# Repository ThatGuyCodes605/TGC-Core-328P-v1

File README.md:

# TGC-Core-328P-v1

## Overview
The **TGC-Core-328P-v1** is an open-source hardware development board. Based on the file naming and standard conventions, it is designed around the "Mega" architecture (typically the Microchip ATme[...] 

This repository contains the complete set of KiCad EDA files necessary to view, modify and manufacture the printed circuit board (PCB).

---

## Features
* **Architecture:** Mega-compatible (ATmega2560) platform.
* **Modern Connectivity:** Upgraded from the legacy USB Type-B to a robust **USB-C 2.0** connector.
* **Native KiCad Design:** Fully designed using KiCad, allowing for easy community modification and inspection.
* **Standard Form Factor:** Designed for compatibility with existing shields and standard development workflows.

---

## Repository Structure

The project is entirely self-contained within the following KiCad design files:

| File Name | Description |
| :--- | :--- |
| `TGC-Core-devboard-Mega-v1.kicad_pro` | The main **KiCad Project file**. Open this file to load the entire project space. |
| `TGC-Core-devboard-Mega-v1.kicad_sch` | The **Schematic file**. Contains the logical connections, components (like the USB-C plug and SW_Push buttons), and wiring. |
| `TGC-Core-devboard-Mega-v1.kicad_pcb` | The **PCB Layout file**. Contains the physical board routing, copper layers, and silkscreen definitions. |
| `TGC-Core-devboard-Mega-v1.png` | A visual render or top-down image of the board design. |

---

## Hardware Specifications (Expected)

*Based on standard Mega-compatible board parameters:*

* **Microcontroller:** ATmega2560 (8-bit AVR)
* **Operating Voltage:** 5V
* **Clock Speed:** 16 MHz
* **Digital I/O Pins:** 54 (of which 15 provide PWM output)
* **Analog Input Pins:** 16
* **Hardware Serial Ports (UARTs):** 4
* **Flash Memory:** 256 KB (8 KB used by bootloader)
* **SRAM:** 8 KB
* **EEPROM:** 4 KB

---

## Getting Started

### 1. Viewing and Editing the Hardware
To view or modify the hardware design:
1. Download and install [KiCad EDA](https://www.kicad.org/). *(Note: Ensure your KiCad version is up to date, as these files use modern KiCad file formatting).*
2. Open the `TGC-Core-devboard-Mega-v1.kicad_pro` file.
3. From the project manager, open the Schematic Editor or PCB Editor to explore the design.

### 2. Software & Programming
Because this board shares the Mega architecture, it is fully compatible with the standard Arduino ecosystem:
1. Open the [Arduino IDE](https://www.arduino.cc/en/software).
2. Connect the board via a USB-C cable to your computer.
3. Go to **Tools > Board** and select **Arduino Mega or Mega 2560**.
4. Go to **Tools > Port** and select the active COM port.
5. Upload your sketches normally.

---

## License

This hardware design and its accompanying documentation are licensed under the **GNU General Public License v3.0 (GPL-3.0-or-later)**.

Summary of your rights under GPLv3:
* You are free to use, study, share, and modify the material.
* If you distribute the work (or a derivative), you must license the whole work under GPLv3 as well (share-alike).
* You must provide source for distributed derivative works and include the GPLv3 license text and copyright notices.

For the full legal text, see the GNU licenses page: https://www.gnu.org/licenses/gpl-3.0.html

Note: To make the change complete, consider adding a `LICENSE` file containing the full GPLv3 text and an explicit copyright line (for example: "Copyright (c) 2026 ThatGuyCodes605"). I can add that file for you if you want.

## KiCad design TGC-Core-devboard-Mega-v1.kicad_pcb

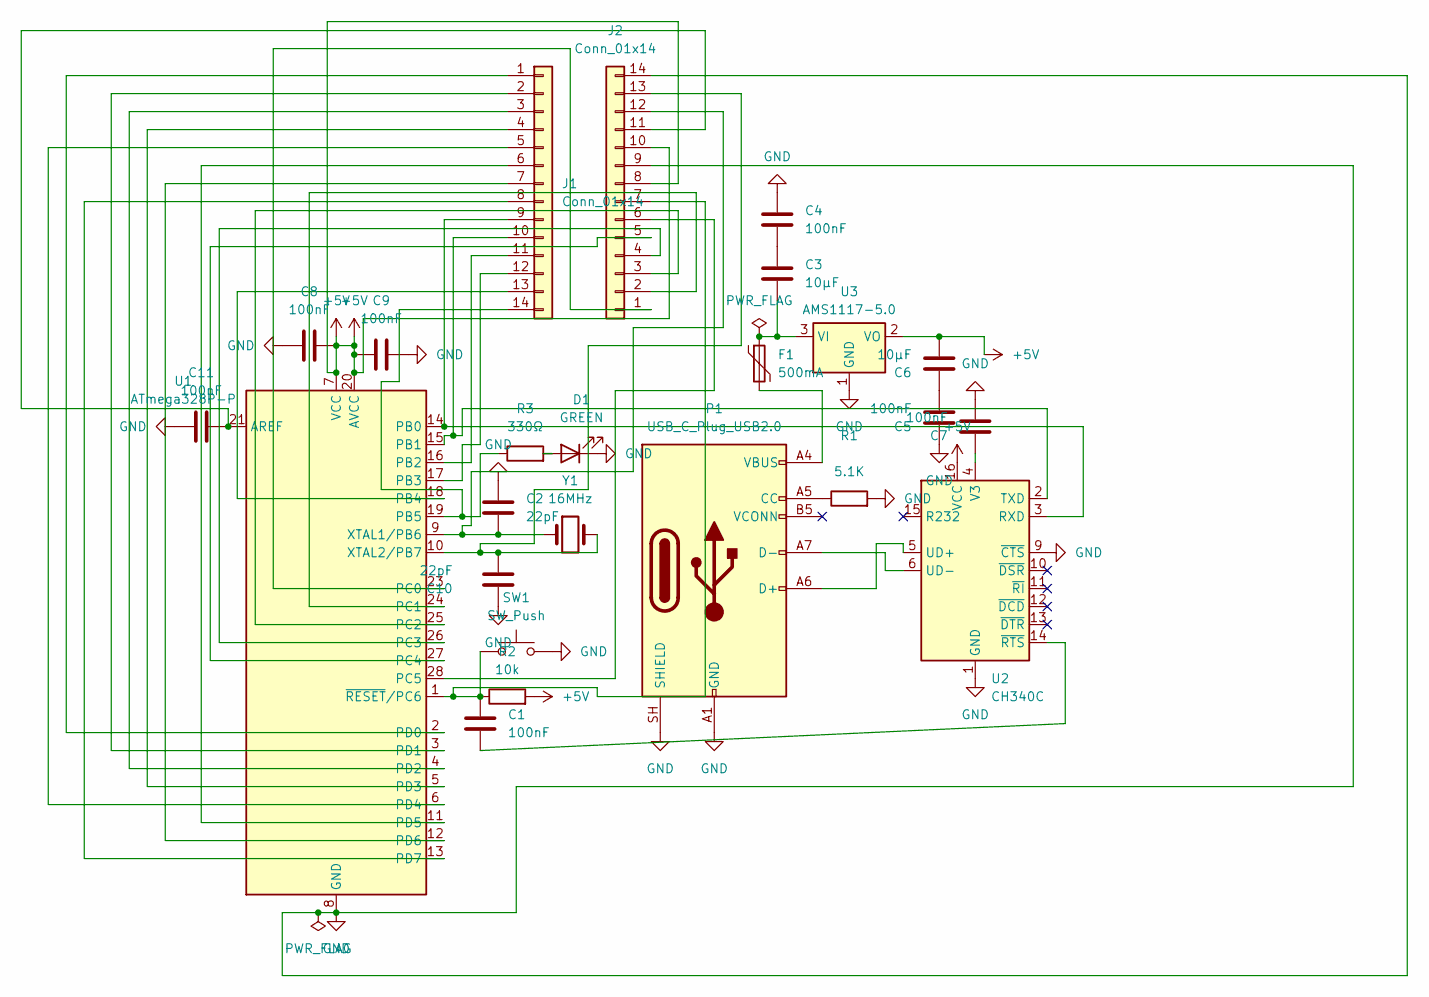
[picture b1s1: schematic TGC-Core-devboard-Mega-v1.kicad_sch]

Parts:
C1, C4, C5, C7, C8, C9, C11: 100nF; C_Disc_D5.0mm_W2.5mm_P2.50mm
C2, C10: 22pF; C_Disc_D5.0mm_W2.5mm_P2.50mm
C3, C6: 10µF; CP_Radial_D5.0mm_P2.00mm
D1: GREEN; LED_D5.0mm_Clear
F1: 500mA; R_Axial_DIN0204_L3.6mm_D1.6mm_P5.08mm_Horizontal
J1, J2: Conn_01x14; PinSocket_1x14_P2.54mm_Vertical
P1: USB_C_Plug_USB2.0; USB_C_Receptacle_HRO_TYPE-C-31-M-12
R1: 5.1K; R_Axial_DIN0204_L3.6mm_D1.6mm_P5.08mm_Horizontal
R2: 10k; R_Axial_DIN0204_L3.6mm_D1.6mm_P5.08mm_Horizontal
R3: 330Ω; R_Axial_DIN0204_L3.6mm_D1.6mm_P5.08mm_Horizontal
SW1: SW_Push; SW_PUSH_6mm
U1: ATmega328P-P; DIP-28_W7.62mm
U2: CH340C; SOIC-16_3.9x9.9mm_P1.27mm
U3: AMS1117-5.0; SOT-223-3_TabPin2
Y1: 16MHz; Crystal_HC49-4H_Vertical

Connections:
+5V: C6.1, C8.1, C9.2, J2.8, J2.10, R2.2, U1.7 (VCC), U1.20 (AVCC), U2.16 (VCC), U3.2 (VO)
GND: C2.1, C4.2, C5.2, C7.1, C8.2, C9.1, C10.1, C11.2, D1.1 (K), J2.9, J2.14, P1.A1 (GND), P1.A12 (GND), P1.B1 (GND), P1.B12 (GND), P1.SH (SHIELD), R1.2, SW1.2, U1.8 (GND), U1.22 (GND), U2.1 (GND), U2.9 (~CTS), U3.1 (GND)
unnamed: C3.2, C4.1
unnamed: C5.1, C6.2
unnamed: D1.2 (A), R3.2
unnamed: F1.2, P1.A4 (VBUS), P1.A9 (VBUS), P1.B4 (VBUS), P1.B9 (VBUS)
unnamed: J1.1, U1.2 (PD0)
unnamed: J1.2, U1.3 (PD1)
unnamed: J1.3, U1.4 (PD2)
unnamed: J1.4, U1.5 (PD3)
unnamed: J1.5, U1.6 (PD4)
unnamed: J1.6, U1.11 (PD5)
unnamed: J1.7, U1.12 (PD6)
unnamed: J1.8, U1.13 (PD7)
unnamed: J1.9, U1.14 (PB0), U2.3 (RXD)
unnamed: J1.10, U1.15 (PB1), U2.2 (TXD)
unnamed: J1.11, U1.16 (PB2)
unnamed: J1.12, U1.17 (PB3)
unnamed: J1.13, U1.18 (PB4)
unnamed: J1.14, R3.1, U1.19 (PB5)
unnamed: J2.1, U1.23 (PC0)
unnamed: J2.2, U1.24 (PC1)
unnamed: J2.3, U1.25 (PC2)
unnamed: J2.4, U1.26 (PC3)
unnamed: J2.5, U1.27 (PC4)
unnamed: J2.6, U1.28 (PC5)
unnamed: C1.1, J2.7, R2.1, SW1.1, U1.1 (~RESET/PC6)
unnamed: C11.1, J2.11, U1.21 (AREF)
unnamed: C2.2, J2.12, U1.9 (XTAL1/PB6), Y1.1
unnamed: C10.2, J2.13, U1.10 (XTAL2/PB7), Y1.2
unnamed: P1.A5 (CC), R1.1
unnamed: P1.A6 (D+), U2.5 (UD+)
unnamed: P1.A7 (D-), U2.6 (UD-)
unnamed: C7.2, U2.4 (V3)
unnamed: C1.2, U2.14 (~RTS)
unnamed: C3.1, F1.1, U3.3 (VI)

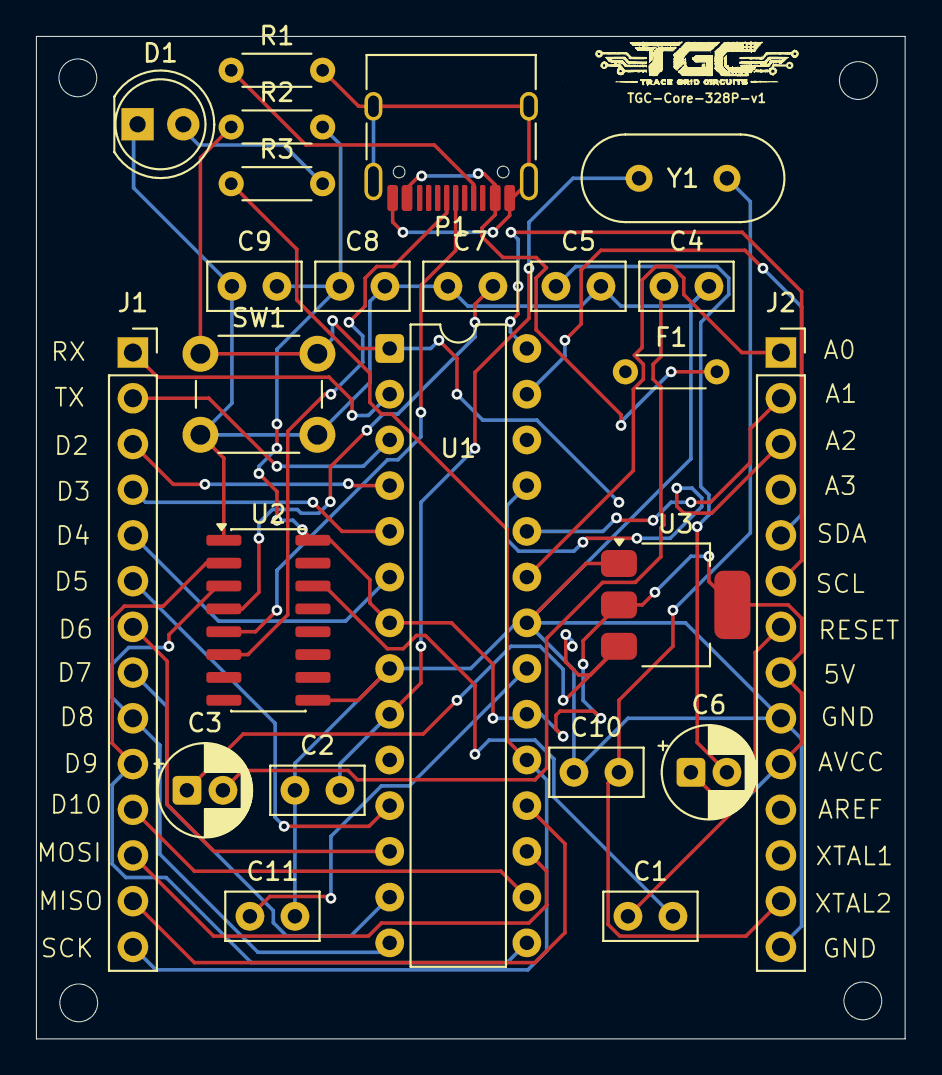
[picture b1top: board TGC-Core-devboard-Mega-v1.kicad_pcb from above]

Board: 4 copper layers, 48.3 x 55.7 mm, 24 parts (0 on the bottom side), 36 nets.

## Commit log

2026-05-31 Revise README for TGC-Core Devboard Mega v1
    Updated the README to reflect the new board name and added detailed features, specifications, and usage instructions.
2026-05-31 Add Creative Commons Attribution 4.0 License
    Added the Creative Commons Attribution 4.0 International Public License to the project.
2026-06-07 Change license to GNU GPLv3 in README
2026-06-07 Add GNU General Public License v3
